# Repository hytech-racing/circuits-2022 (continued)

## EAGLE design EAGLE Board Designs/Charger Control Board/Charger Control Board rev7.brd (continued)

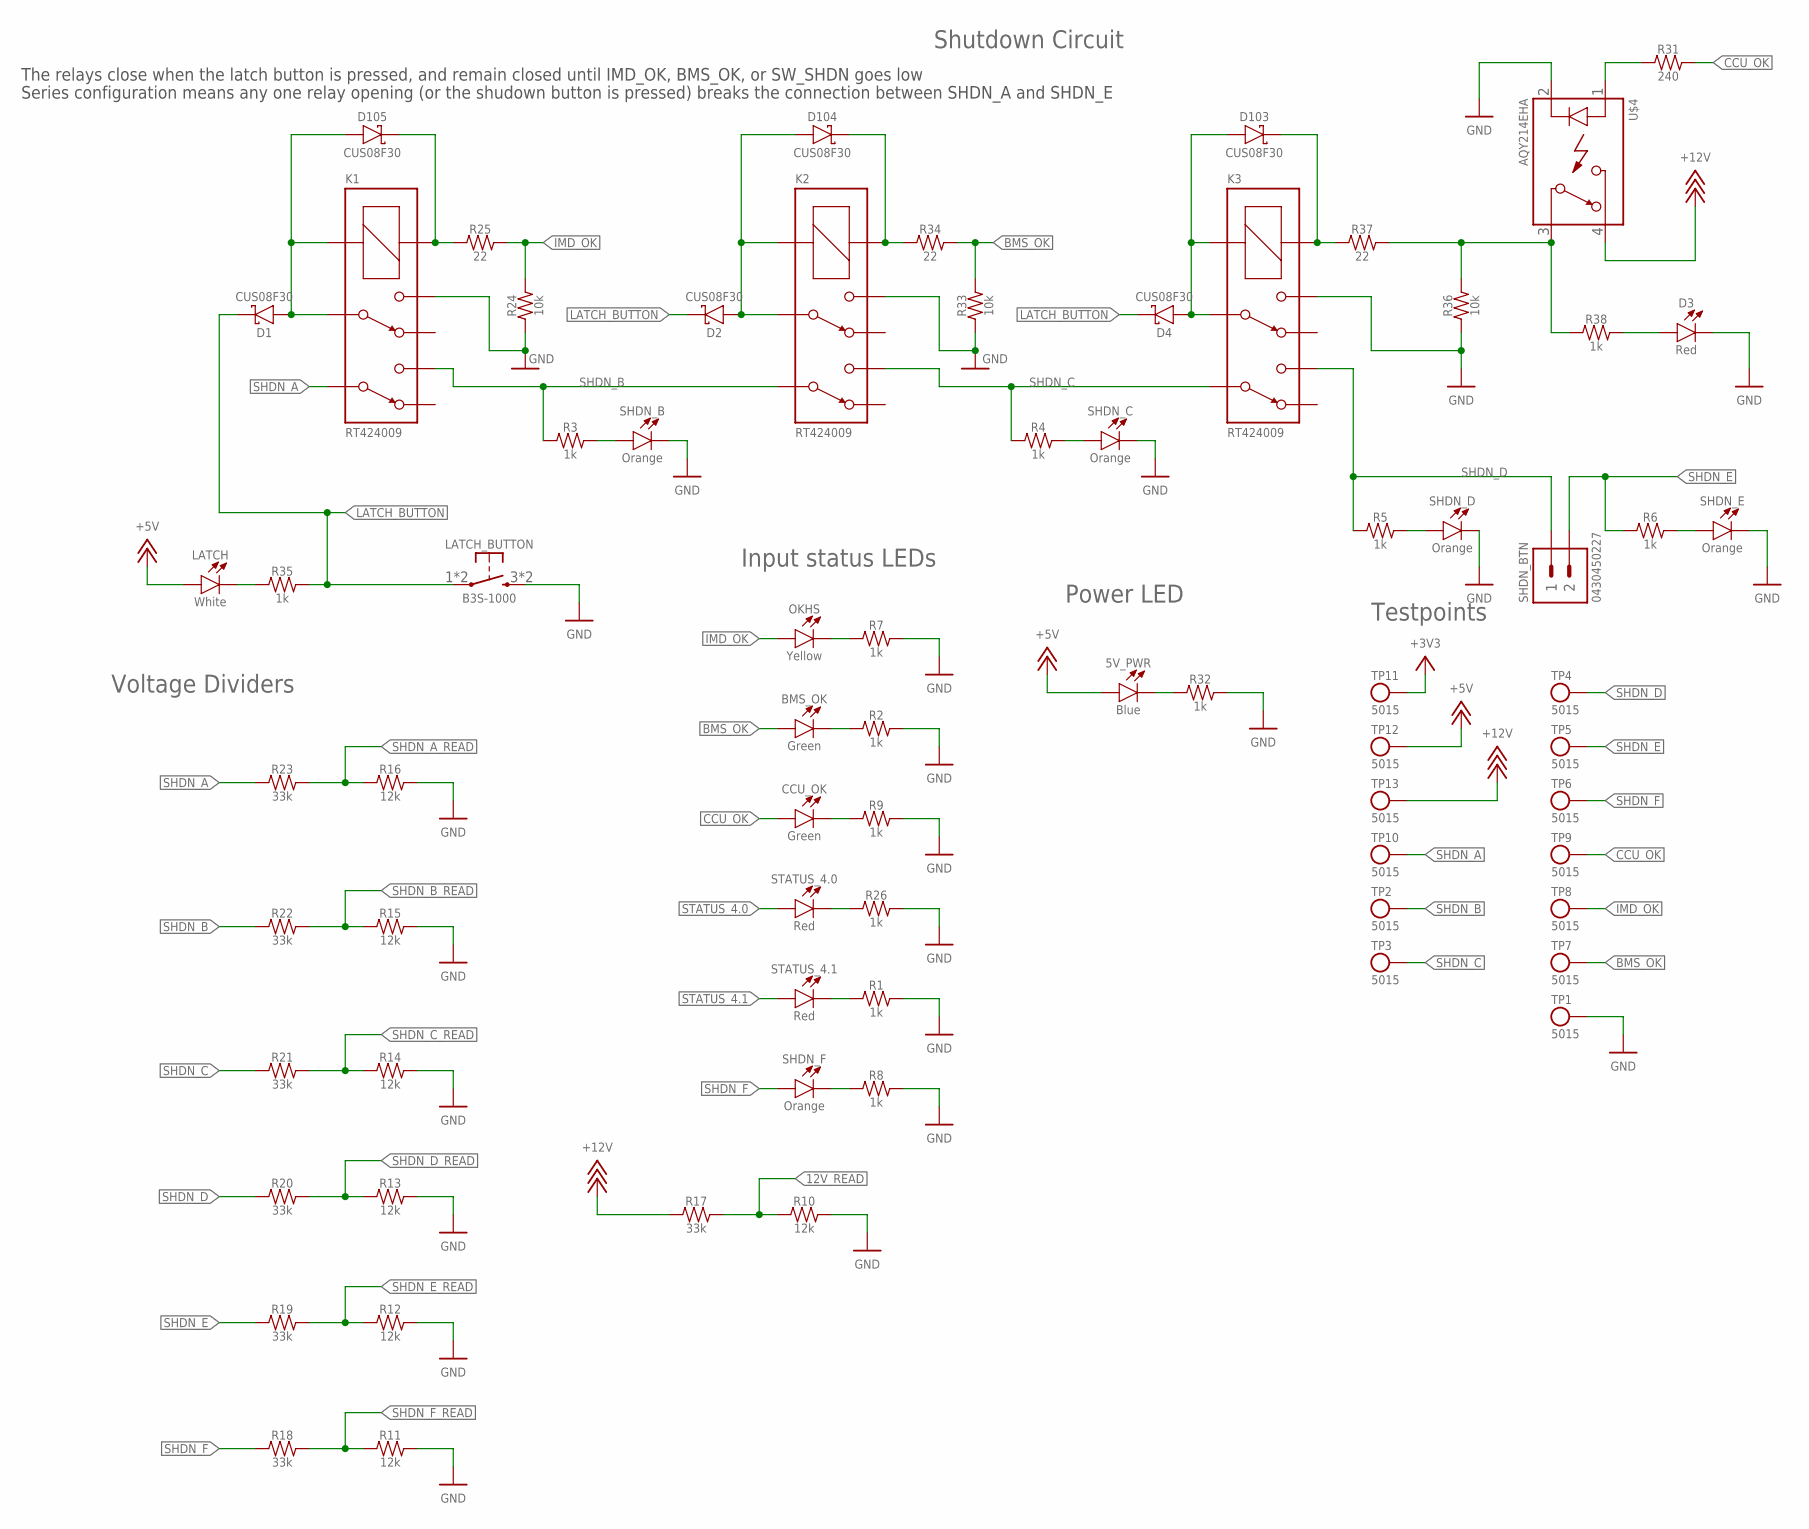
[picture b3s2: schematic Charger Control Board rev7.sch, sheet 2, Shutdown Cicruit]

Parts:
5V_PWR: LED_0603_BLUE; 0603-LED
BMS_OK: LED_0603_GREEN; 0603-LED
CCU_OK: LED_0603_GREEN; 0603-LED
D1, D2, D4, D103, D104, D105: SCHOTTKY_SOD323_30V; SOD-323
D3: LED_0603_RED; 0603-LED
K1, K2, K3: RELAY_DPDT; RT*2*
LATCH: LED_0603_WHITE; 0603-LED
LATCH_BUTTON: BUTTON; B3S-100X
OKHS: LED_0603_YELLOW; 0603-LED
R1, R2, R3, R4, R5, R6, R7, R8, R9, R26, R32, R35, R38: RESISTOR_0603_1K; 0603-RES
R10, R11, R12, R13, R14, R15, R16: RESISTOR_0603_12K; 0603-RES
R17, R18, R19, R20, R21, R22, R23: RESISTOR_0603_33K; 0603-RES
R24, R33, R36: RESISTOR_0603_10K; 0603-RES
R25, R34, R37: RESISTOR_0603_22; 0603-RES
R31: RESISTOR_0603_240; 0603-RES
SHDN_B: LED_0603_ORANGE; 0603-LED
SHDN_BTN: CONNECTOR-2_μF_T_V_; MOLEX_MICROFIT_PTH_VERTICAL_02_DUAL
SHDN_C: LED_0603_ORANGE; 0603-LED
SHDN_D: LED_0603_ORANGE; 0603-LED
SHDN_E: LED_0603_ORANGE; 0603-LED
SHDN_F: LED_0603_ORANGE; 0603-LED
STATUS_4.0, STATUS_4.1: LED_0603_RED; 0603-LED
TP1, TP2, TP3, TP4, TP5, TP6, TP7, TP8, TP9, TP10, TP11, TP12, TP13: TEST_POINT; 5015
U$4: RELAY_SOLIDSTATE_NO; DIP-4

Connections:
12V_READ: R10.1, R17.2; also elsewhere on the board
+3V3: TP11.1; also elsewhere on the board
+5V: 5V_PWR.2 (A), LATCH.2 (A), TP12.1; also elsewhere on the board
+12V: R17.1, TP13.1, U$4.4 (CONTACT2); also elsewhere on the board
BMS_OK: BMS_OK.2 (A), R33.2, R34.2, TP7.1; also elsewhere on the board
CCU_OK: CCU_OK.2 (A), R31.2, TP9.1; also elsewhere on the board
GND: D3.1 (C), K1.14 (4), K2.14 (4), K3.14 (4), LATCH_BUTTON.3 (S), LATCH_BUTTON.4 (S), R1.2, R2.2, R7.2, R8.2, R9.2, R10.2, R11.2, R12.2, R13.2, R14.2, R15.2, R16.2, R24.1, R26.2, R32.2, R33.1, R36.1, SHDN_B.1 (C), SHDN_C.1 (C), SHDN_D.1 (C), SHDN_E.1 (C), TP1.1, U$4.2 (CONTROL-); also elsewhere on the board
IMD_OK: OKHS.2 (A), R24.2, R25.2, TP8.1; also elsewhere on the board
LATCH_BUTTON: D1.C, D2.C, D4.C, LATCH_BUTTON.1, LATCH_BUTTON.2, R35.2
unnamed: R8.1, SHDN_F.1 (C)
unnamed: R31.1, U$4.1 (CONTROL+)
unnamed: D1.A, D105.A, K1.11 (3), K1.A2 (COIL-)
unnamed: D105.C, K1.A1 (COIL+), R25.1
unnamed: D104.C, K2.A1 (COIL+), R34.1
unnamed: D2.A, D104.A, K2.11 (3), K2.A2 (COIL-)
unnamed: D103.C, K3.A1 (COIL+), R37.1
unnamed: R36.2, R37.2, R38.1, U$4.3 (CONTACT1)
unnamed: LATCH.1 (C), R35.1
unnamed: R5.2, SHDN_D.2 (A)
unnamed: R6.2, SHDN_E.2 (A)
unnamed: D4.A, D103.A, K3.11 (3), K3.A2 (COIL-)
unnamed: D3.2 (A), R38.2
unnamed: R4.2, SHDN_C.2 (A)
unnamed: R3.2, SHDN_B.2 (A)
unnamed: OKHS.1 (C), R7.1
unnamed: BMS_OK.1 (C), R2.1
unnamed: CCU_OK.1 (C), R9.1
unnamed: R26.1, STATUS_4.0.1 (C)
unnamed: 5V_PWR.1 (C), R32.1
unnamed: R1.1, STATUS_4.1.1 (C)
SHDN_A: K1.21 (6), R23.1, TP10.1; also elsewhere on the board
SHDN_A_READ: R16.1, R23.2; also elsewhere on the board
SHDN_B: K1.24 (5), K2.21 (6), R3.1, R22.1, TP2.1
SHDN_B_READ: R15.1, R22.2; also elsewhere on the board
SHDN_C: K2.24 (5), K3.21 (6), R4.1, R21.1, TP3.1
SHDN_C_READ: R14.1, R21.2; also elsewhere on the board
SHDN_D: K3.24 (5), R5.1, R20.1, SHDN_BTN.1, TP4.1
SHDN_D_READ: R13.1, R20.2; also elsewhere on the board
SHDN_E: R6.1, R19.1, SHDN_BTN.2, TP5.1; also elsewhere on the board
SHDN_E_READ: R12.1, R19.2; also elsewhere on the board
SHDN_F: R18.1, SHDN_F.2 (A), TP6.1; also elsewhere on the board
SHDN_F_READ: R11.1, R18.2; also elsewhere on the board
STATUS_4.0: STATUS_4.0.2 (A); also elsewhere on the board
STATUS_4.1: STATUS_4.1.2 (A); also elsewhere on the board

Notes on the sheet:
Input status LEDs
Power LED
Voltage Dividers
Shutdown Circuit
Testpoints
The relays close when the latch button is pressed, and remain closed until IMD_OK, BMS_OK, or SW_SHDN goes low
Series configuration means any one relay opening (or the shudown button is pressed) breaks the connection between SHDN_A and SHDN_E

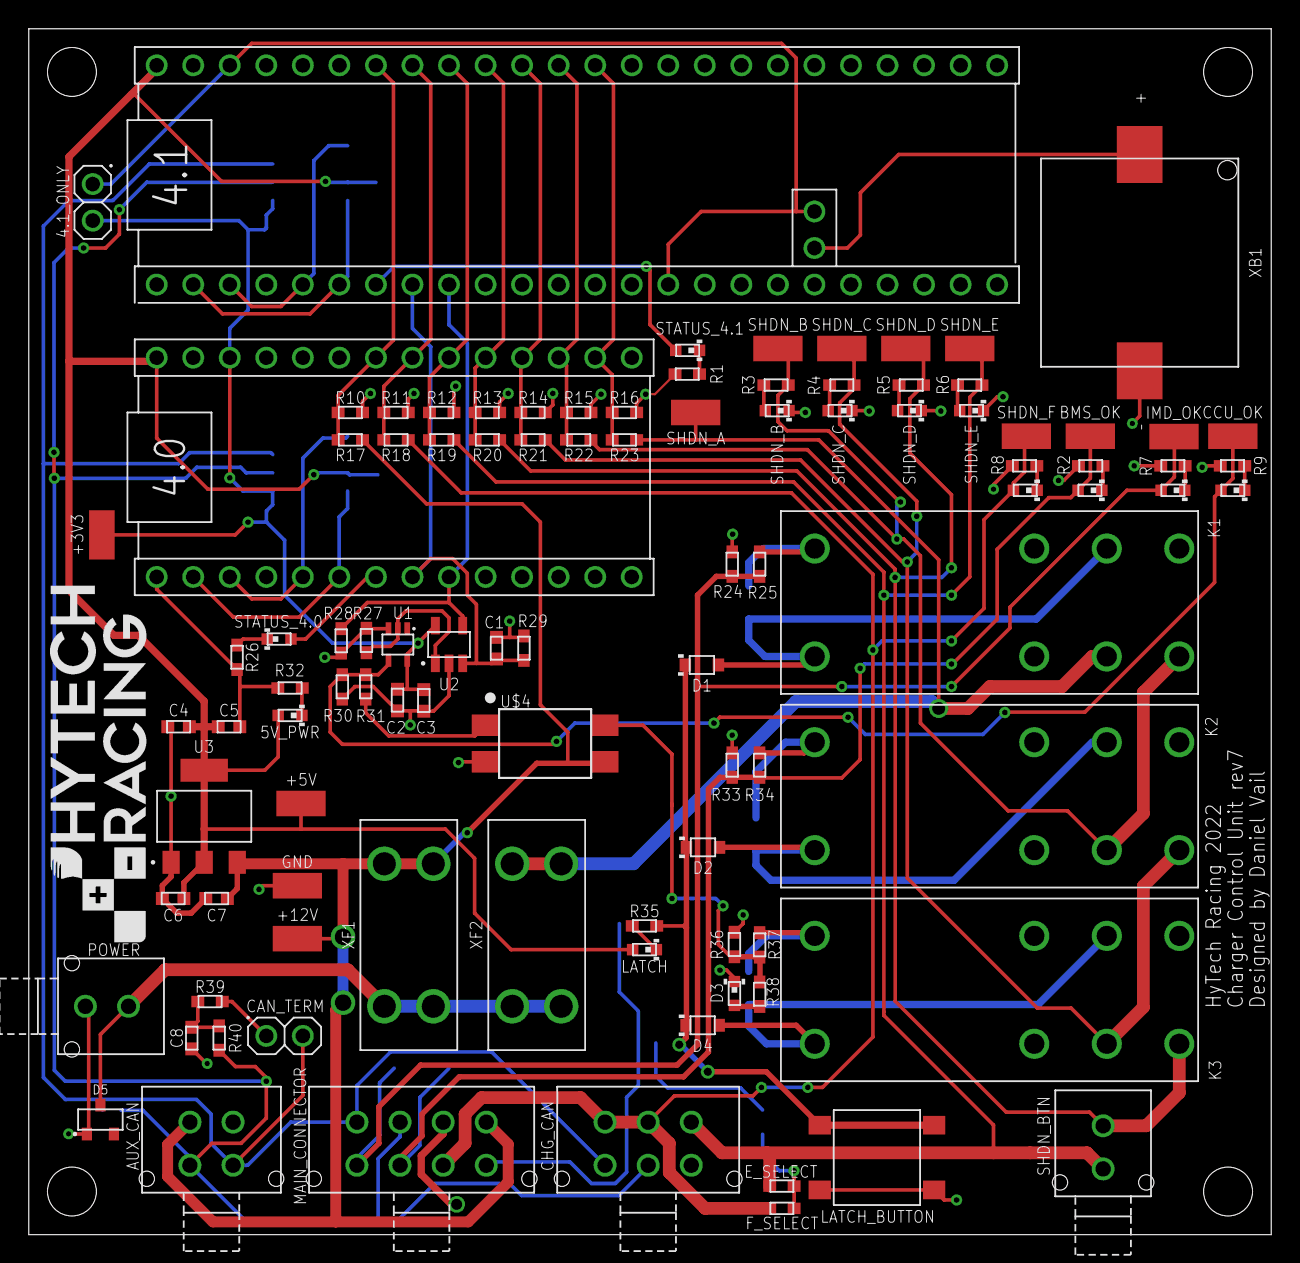
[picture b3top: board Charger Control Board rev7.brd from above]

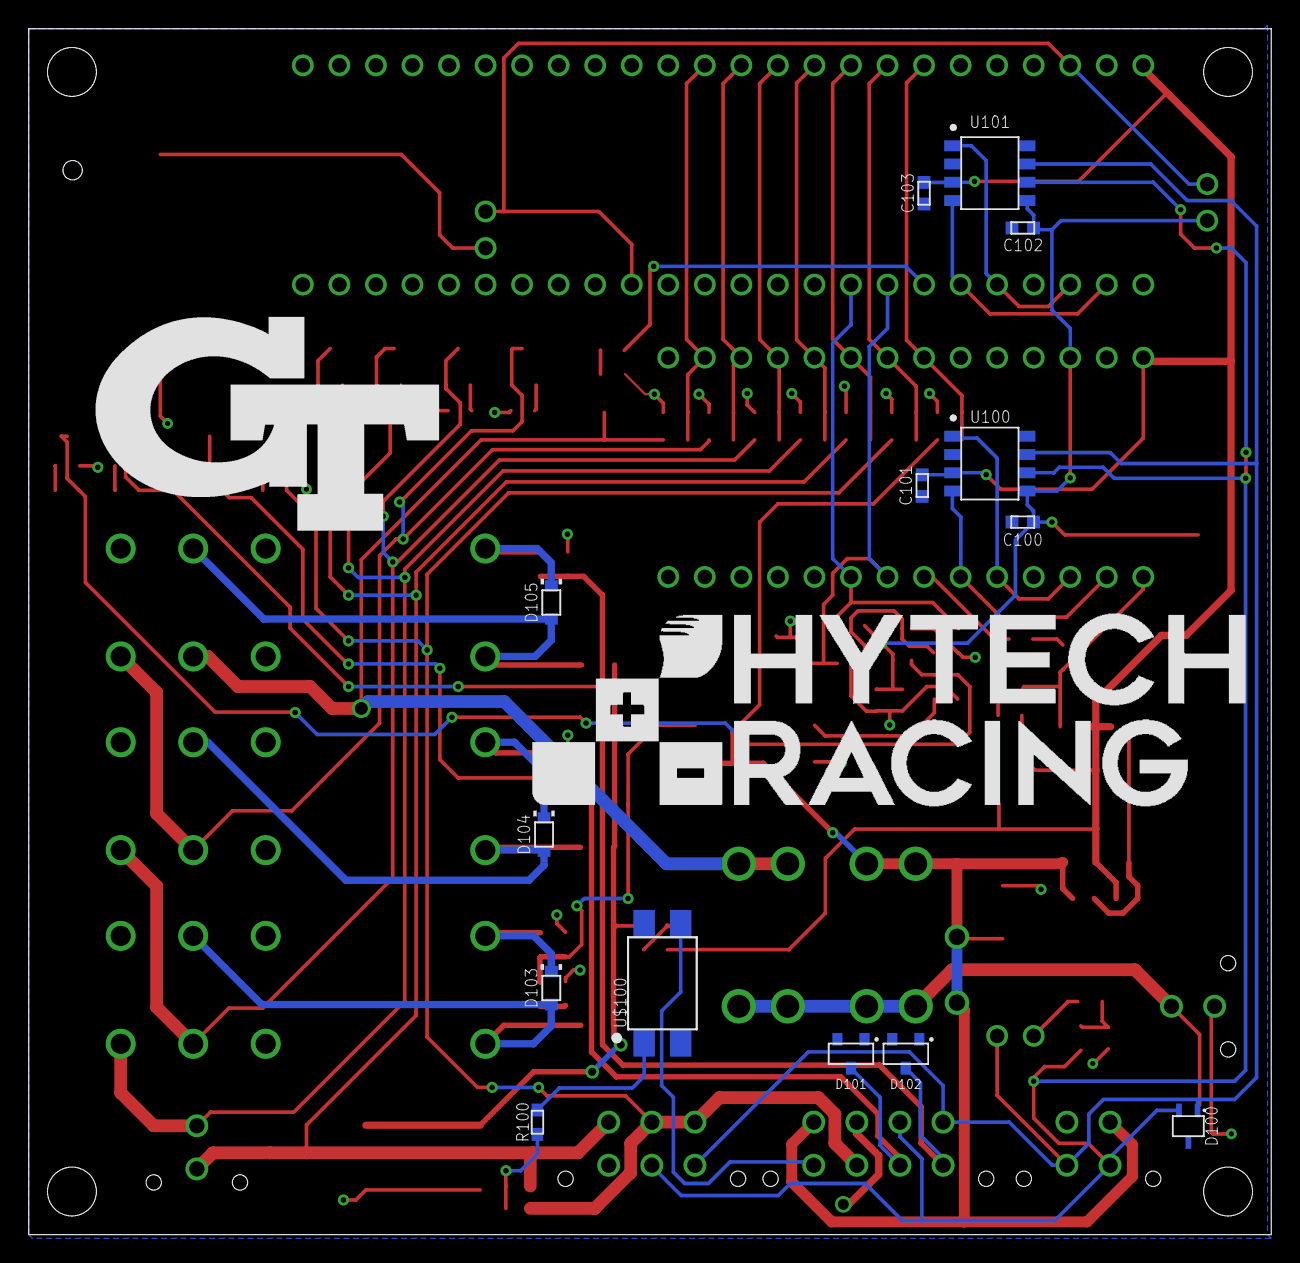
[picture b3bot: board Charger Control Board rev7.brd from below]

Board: 2 copper layers, 86.4 x 83.8 mm, 121 parts (16 on the bottom side), 61 nets.

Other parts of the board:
U$1, U$2, U$6, U$7: MOUNTING_M3
U$5: LOGO_HYTECH_MEDIUM
U$9: LOGO_HYTECH_LARGE
U$10: LOGO_GT_LARGE

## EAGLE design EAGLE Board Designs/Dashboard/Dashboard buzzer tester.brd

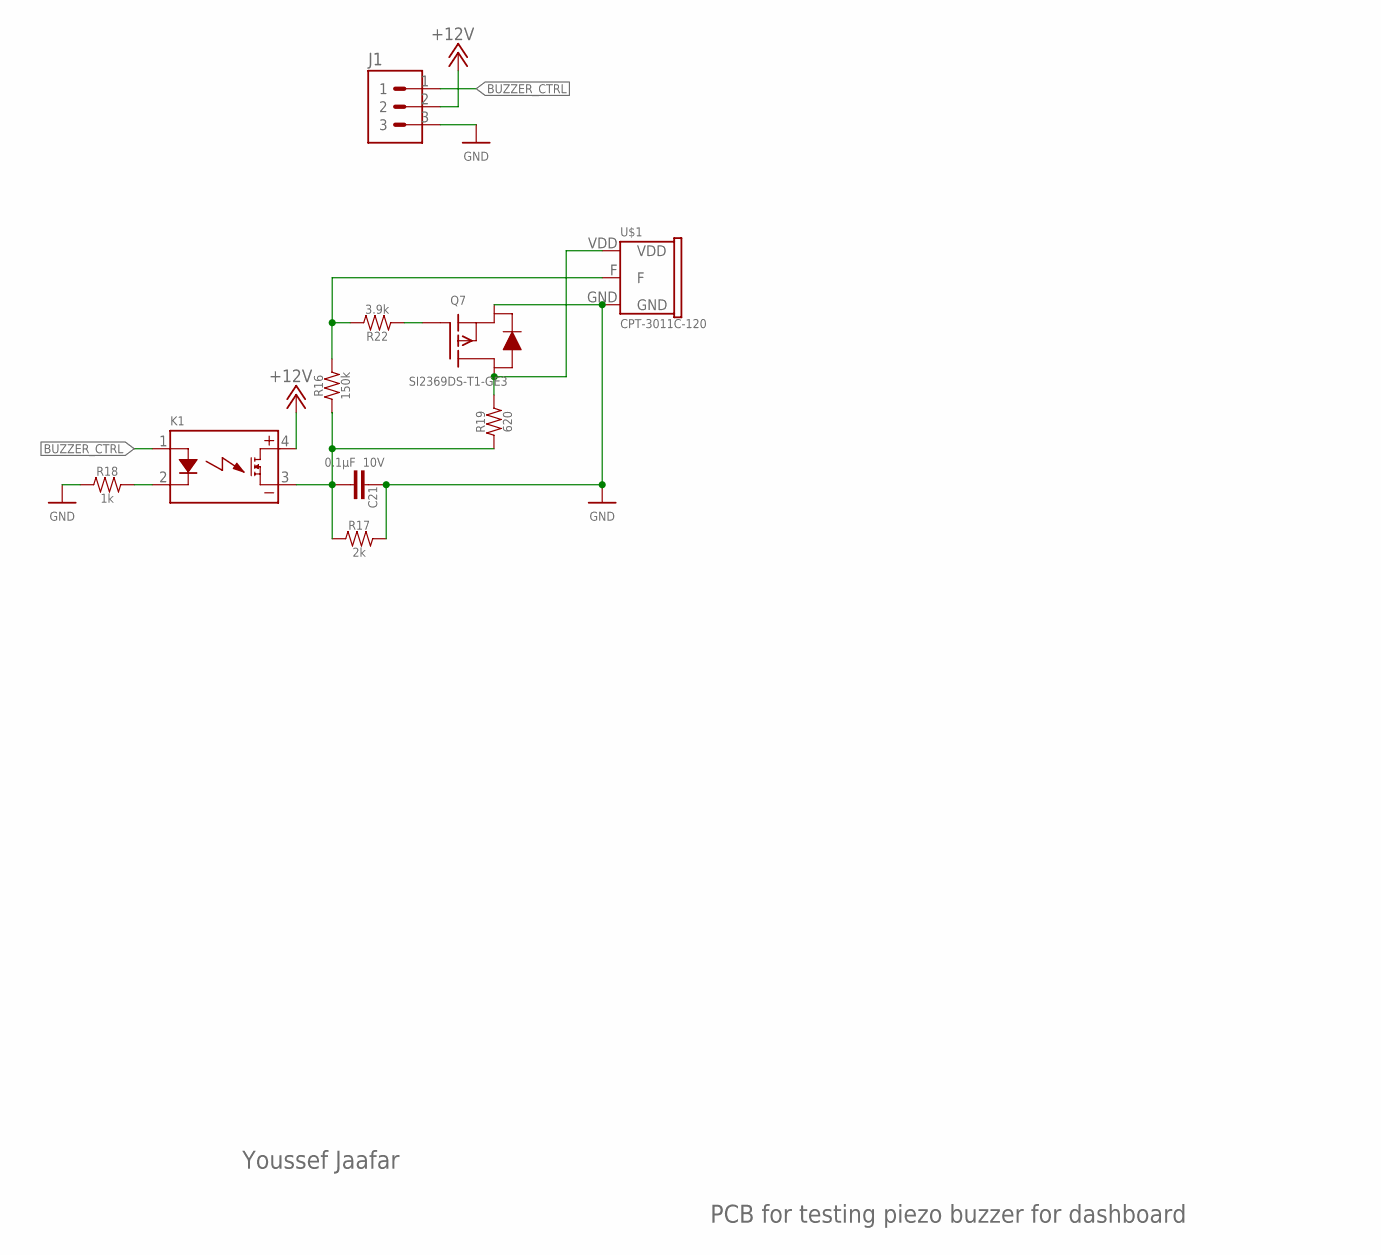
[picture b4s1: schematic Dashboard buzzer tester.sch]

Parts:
C21: CAPACITOR_0603_10V_0.1UF; 0603-CAP
J1: CONNECTOR-3; 1X03
K1: CPC1002N; SOP-04
Q7: TRANSISTOR_P_MOS_SOT23_SI2369DS-T1-GE3; SOT-23
R16: RESISTOR_0603_150K; 0603-RES
R17: RESISTOR_0603_2K; 0603-RES
R18: RESISTOR_0603_1K; 0603-RES
R19: RESISTOR_0603_620; 0603-RES
R22: RESISTOR_0603_3.9K; 0603-RES
U$1: BUZZER_3_PIN_CPT-3011C-120; CPT-3011C-120

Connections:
+12V: J1.2, K1.4 (DC+)
BUZZER_CTRL: J1.1, K1.1 (CONTROL+)
BUZZER_OUT: C21.1, K1.3 (DC-), R16.1, R17.1, R19.1
GND: C21.2, J1.3, Q7.2 (S), R17.2, R18.1, U$1.GND
unnamed: Q7.3 (D), R19.2, U$1.VDD
unnamed: Q7.1 (G), R22.1
unnamed: R16.2, R22.2, U$1.F
unnamed: K1.2 (CONTROL-), R18.2

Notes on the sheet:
Youssef Jaafar
PCB for testing piezo buzzer for dashboard

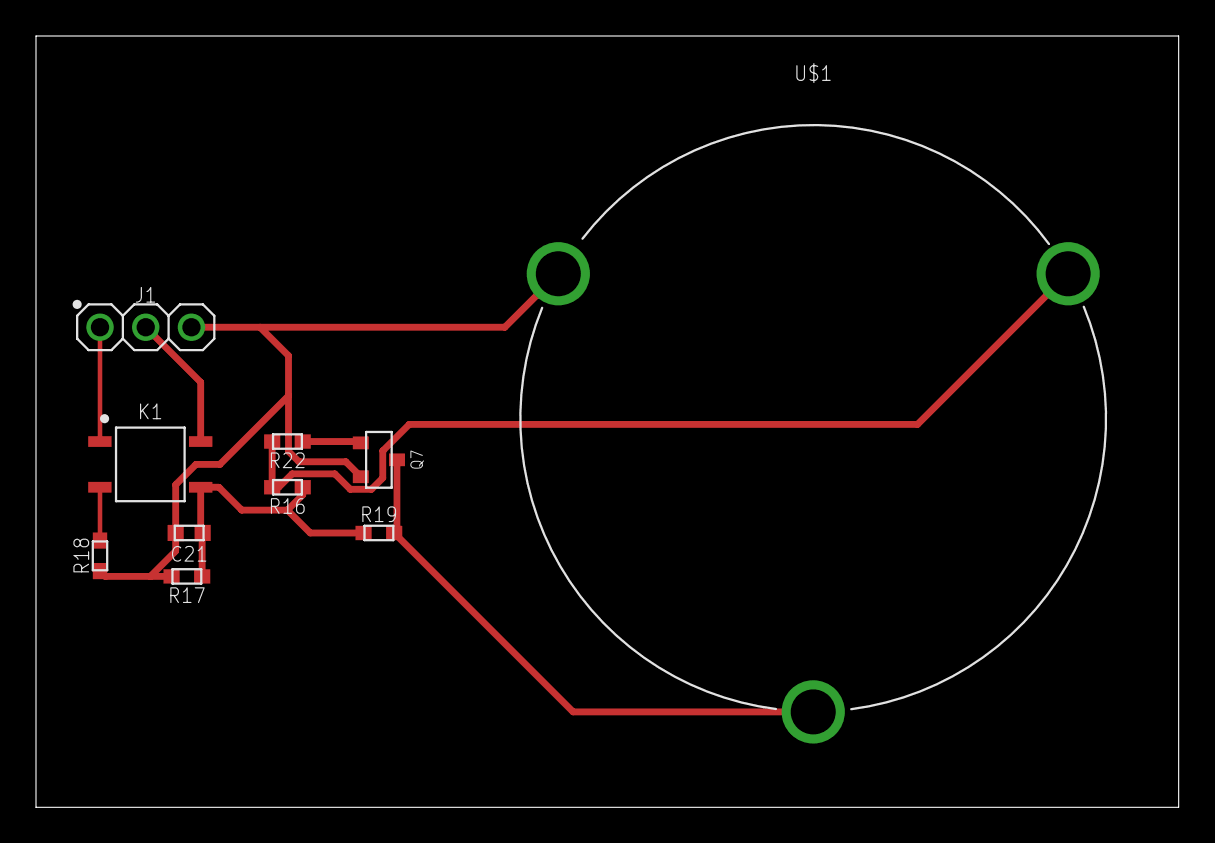
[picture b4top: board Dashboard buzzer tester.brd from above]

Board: 2 copper layers, 63.5 x 42.9 mm, 10 parts (0 on the bottom side), 8 nets.

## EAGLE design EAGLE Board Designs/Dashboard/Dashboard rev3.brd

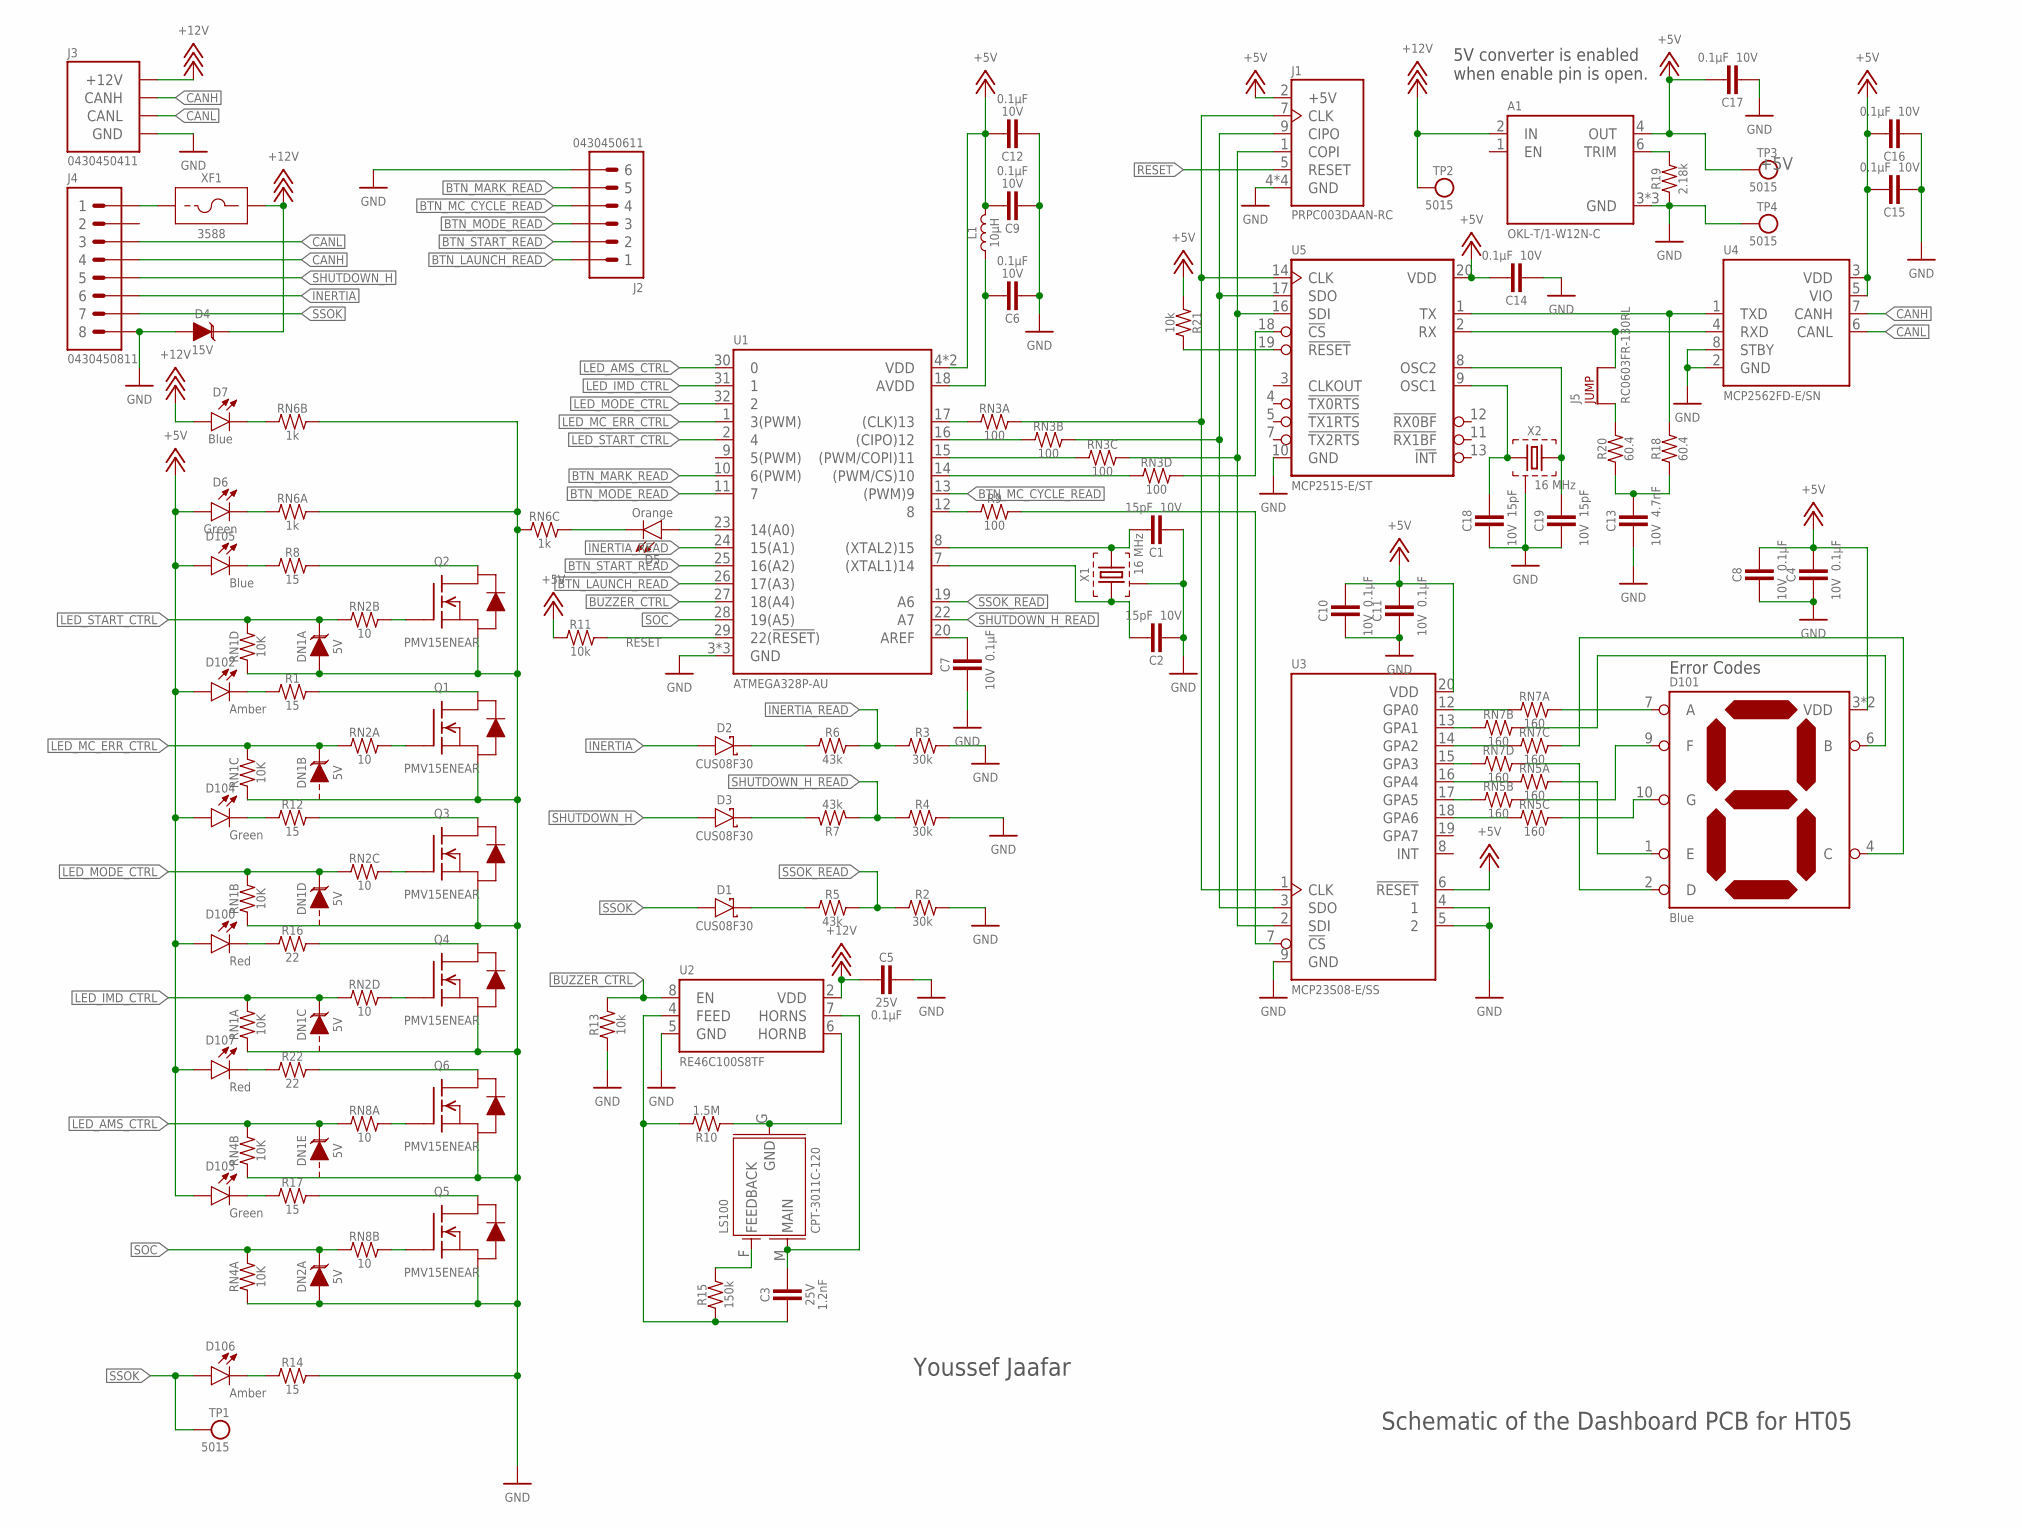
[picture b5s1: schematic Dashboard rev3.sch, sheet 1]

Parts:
A1: OKL-T/1-W12N-COKL; OKL-T/1-W12
C1, C2, C18, C19: CAPACITOR_0603_10V_15PF; 0603-CAP
C3: CAPACITOR_0603_25V_1.2NF; 0603-CAP
C4, C6, C7, C8, C9, C10, C11, C12, C14, C15, C16, C17: CAPACITOR_0603_10V_0.1UF; 0603-CAP
C5: CAPACITOR_0603_25V_0.1UF; 0603-CAP
C13: CAPACITOR_0603_10V_4.7NF; 0603-CAP
D1, D2, D3: SCHOTTKY_SOD323_30V; SOD-323
D4: TVS_15V; SOT-23
D5: LED_0603_ORANGE; 0603-LED
D6: LED_0603_GREEN; 0603-LED
D7: LED_0603_BLUE; 0603-LED
D100, D107: LED_2835_RED; 2835-LED
D101: LED_7_SEGMENT_BLUE_DSM7TA; DSM7T
D102, D106: LED_2835_AMBER; 2835-LED
D103, D104: LED_2835_GREEN; 2835-LED
D105: LED_2835_BLUE; 2835-LED
DN1, DN2: TVS_ARRAY_5V; SOT-363
J1: CONNECTOR-AVR-ISP_2X05_SMD; 2X05_SMD
J2: CONNECTOR-6_μF_S_RA_; MOLEX_MICROFIT_SMD_RIGHTANGLE_06_DUAL
J3: CONNECTOR-CAN_μF_S_RA_; MOLEX_MICROFIT_SMD_RIGHTANGLE_04_DUAL
J4: CONNECTOR-8_μF_S_RA_; MOLEX_MICROFIT_SMD_RIGHTANGLE_08_DUAL
J5: JUMPER_0603_; 0603-RES
L1: INDUCTOR_LQM18DH100M70_10UH; 0603-IND
LS100: BUZZER_3_PIN_CPT-3011C-120; CPT-3011C-120
Q1, Q2, Q3, Q4, Q5, Q6: TRANSISTOR_N_MOS__PMV15ENEA; SOT-23
R1, R8, R12, R14, R17: RESISTOR_0603_15; 0603-RES
R2, R3, R4: RESISTOR_0603_30K; 0603-RES
R5, R6, R7: RESISTOR_0603_43K; 0603-RES
R9: RESISTOR_0603_100; 0603-RES
R10: RESISTOR_0603_1.5M; 0603-RES
R11, R13, R21: RESISTOR_0603_10K; 0603-RES
R15: RESISTOR_0603_150K; 0603-RES
R16, R22: RESISTOR_0805_22; 0805-RES
R18, R20: RESISTOR_0603_60.4; 0603-RES
R19: RESISTOR_0603_2.18K; 0603-RES
RN1, RN4: RESISTOR_NETWORK_4_10K; 1206-RES-ARRAY
RN2, RN8: RESISTOR_NETWORK_4_10; 1206-RES-ARRAY
RN3: RESISTOR_NETWORK_4_100; 1206-RES-ARRAY
RN5, RN7: RESISTOR_NETWORK_4_160; 1206-RES-ARRAY
RN6: RESISTOR_NETWORK_4_1K; 1206-RES-ARRAY
TP1, TP2, TP3, TP4: TEST_POINT; 5015
U1: ATMEGA328P-AU; TQFP-32
U2: RE46C100; SOIC-08(NARROW,0.15")
U3: MCP23S08; SSOP-20
U4: MCP2562FD; SOIC-08(NARROW,0.15")
U5: MCP2515; TSSOP-20
X1, X2: CRYSTAL_16MHZ; ECX-42
XF1: FUSE_HOLDER_MINIBLADESMD; 3588

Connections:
+5V: A1.4 (OUT), C4.1, C8.1, C9.1, C10.1, C11.1, C12.1, C14.1, C15.1, C16.1, C17.1, D6.2 (A), D100.A, D101.3 (VDD), D101.8 (VDD), D102.A, D103.A, D104.A, D105.A, D107.A, J1.2 (+5V), L1.2, R11.1, R21.1, TP3.1, U1.4 (VDD), U1.6 (VDD), U3.6 (!RESET), U3.20 (VDD), U4.3 (VDD), U4.5 (VIO), U5.20 (VDD)
+12V: A1.2 (IN), C5.2, D4.3 (C), D7.2 (A), J3.1 (+12V), TP2.1, U2.2 (VDD), XF1.3 (2), XF1.4 (2)
A2: RN7.1, U3.12 (GPA0)
B2: RN7.2 (1), U3.13 (GPA1)
BTN_LAUNCH_READ: J2.1, U1.26 (17(A3))
BTN_MARK_READ: J2.5, U1.10 (6(PWM))
BTN_MC_CYCLE_READ: J2.4, U1.13 ((PWM)9)
BTN_MODE_READ: J2.3, U1.11 (7)
BTN_START_READ: J2.2, U1.25 (16(A2))
BUZZER_CTRL: R13.2, U1.27 (18(A4)), U2.8 (EN)
C2: RN7.3 (1), U3.14 (GPA2)
CANH: J3.4 (CANH), J4.4, U4.7 (CANH)
CANL: J3.3 (CANL), J4.3, U4.6 (CANL)
D2: RN7.4 (1), U3.15 (GPA3)
E2: RN5.1, U3.16 (GPA4)
F2: RN5.2 (1), U3.17 (GPA5)
G2: RN5.3 (1), U3.18 (GPA6)
GND: A1.3 (GND), A1.7 (GND), A1.11 (GND), C1.2, C2.2, C4.2, C5.1, C6.2, C7.2, C8.2, C9.2, C10.2, C11.2, C12.2, C13.2, C14.2, C15.2, C16.2, C17.2, C18.2, C19.2, D4.1 (A), DN1.2 (A), DN2.2 (A), J1.4 (GND), J1.6 (GND), J1.8 (GND), J1.10 (GND), J2.6, J3.2 (GND), J4.8, Q1.2 (S), Q2.2 (S), Q3.2 (S), Q4.2 (S), Q5.2 (S), Q6.2 (S), R2.2, R3.2, R4.2, R13.1, R14.2, R19.1, RN1.1, RN1.2 (1), RN1.3 (1), RN1.4 (1), RN4.1, RN4.2 (1), RN6.3 (1), RN6.7 (2), RN6.8 (2), TP4.1, U1.3 (GND), U1.5 (GND), U1.21 (GND), U2.5 (GND), U3.4 (1), U3.5 (2), U3.9 (GND), U4.2 (GND), U4.8 (STBY), U5.10 (GND), X1.2 (GND), X1.4 (GND), X2.2 (GND), X2.4 (GND)
INERTIA: D2.A, J4.6
INERTIA_READ: R3.1, R6.2, U1.24 (15(A1))
LED_AMS_CTRL: DN1.6 (C), RN4.7 (2), RN8.1, U1.30 (0)
LED_IMD_CTRL: DN1.4 (C), RN1.8 (2), RN2.4 (1), U1.31 (1)
LED_MC_ERR_CTRL: DN1.3 (C), RN1.6 (2), RN2.1, U1.1 (3(PWM))
LED_MODE_CTRL: DN1.5 (C), RN1.7 (2), RN2.3 (1), U1.32 (2)
LED_START_CTRL: DN1.1 (C), RN1.5 (2), RN2.2 (1), U1.2 (4)
unnamed: C18.1, U5.9 (OSC1), X2.1
unnamed: D102.C, R1.1
unnamed: C1.1, U1.8 ((XTAL2)15), X1.3
unnamed: C7.1, U1.20 (AREF)
unnamed: Q1.3 (D), R1.2
unnamed: Q3.3 (D), R12.2
unnamed: Q4.3 (D), R16.2
unnamed: Q6.3 (D), R22.2
unnamed: Q5.3 (D), R17.2
unnamed: Q2.1 (G), RN2.7 (2)
unnamed: C2.1, U1.7 ((XTAL1)14), X1.1
unnamed: J1.7 (CLK), RN3.8 (2), U3.1 (CLK), U5.14 (CLK)
unnamed: D101.7 (A), RN7.8 (2)
unnamed: D101.6 (B), RN7.7 (2)
unnamed: D101.4 (C), RN7.6 (2)
unnamed: D101.10 (G), RN5.6 (2)
unnamed: D101.9 (F), RN5.7 (2)
unnamed: D101.1 (E), RN5.8 (2)
unnamed: D101.2 (D), RN7.5 (2)
unnamed: RN3.4 (1), U1.14 ((PWM/CS)10)
unnamed: D6.1 (C), RN6.1
unnamed: Q1.1 (G), RN2.8 (2)
unnamed: J1.9 (CIPO), RN3.7 (2), U3.3 (SDO), U5.17 (SDO)
unnamed: D104.C, R12.1
unnamed: D100.C, R16.1
unnamed: D106.C, R14.1
unnamed: D107.C, R22.1
unnamed: C3.1, LS100.M (MAIN), U2.7 (HORNS)
unnamed: R9.1, U1.12 (8)
unnamed: A1.6 (TRIM), R19.2
unnamed: D105.C, R8.1
unnamed: D1.C, R5.1
unnamed: D3.C, R7.1
unnamed: Q2.3 (D), R8.2
unnamed: Q4.1 (G), RN2.5 (2)
unnamed: Q3.1 (G), RN2.6 (2)
unnamed: Q5.1 (G), RN8.7 (2)
unnamed: Q6.1 (G), RN8.8 (2)
unnamed: LS100.G (GND), R10.1, U2.6 (HORNB)
unnamed: D103.C, R17.1
unnamed: J5.2, U4.4 (RXD), U5.2 (RX)
unnamed: C19.1, U5.8 (OSC2), X2.3
unnamed: J4.1, XF1.1, XF1.2 (1)
unnamed: D5.2 (A), U1.23 (14(A0))
unnamed: RN3.1, U1.17 ((CLK)13)
unnamed: R21.2, U5.19 (!RESET)
unnamed: RN3.2 (1), U1.16 ((CIPO)12)
unnamed: RN3.3 (1), U1.15 ((PWM/COPI)11)
unnamed: C3.2, R10.2, R15.1, U2.4 (FEED)
unnamed: J5.1, R20.2
unnamed: C13.1, R18.1, R20.1
unnamed: R18.2, U4.1 (TXD), U5.1 (TX)
unnamed: LS100.F (FEEDBACK), R15.2
unnamed: J1.1 (COPI), RN3.6 (2), U3.2 (SDI), U5.16 (SDI)
unnamed: RN3.5 (2), U5.18 (!CS)
unnamed: R9.2, U3.7 (!CS)
unnamed: C6.1, L1.1, U1.18 (AVDD)
unnamed: D2.C, R6.1
RESET: J1.5 (RESET), R11.2, U1.29 (22(!RESET!))
SHUTDOWN_H: D3.A, J4.5
SHUTDOWN_H_READ: R4.1, R7.2, U1.22 (A7)
SOC: DN2.1 (C), RN4.8 (2), RN8.2 (1), U1.28 (19(A5))
SSOK: D1.A, D106.A, J4.7, TP1.1
SSOK_READ: R2.1, R5.2, U1.19 (A6)
STATUS_12V: D7.1 (C), RN6.2 (1)
STATUS_TEENSY: D5.1 (C), RN6.6 (2)

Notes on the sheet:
Youssef Jaafar
Schematic of the Dashboard PCB for HT05
Error Codes
5V converter is enabled when enable pin is open.

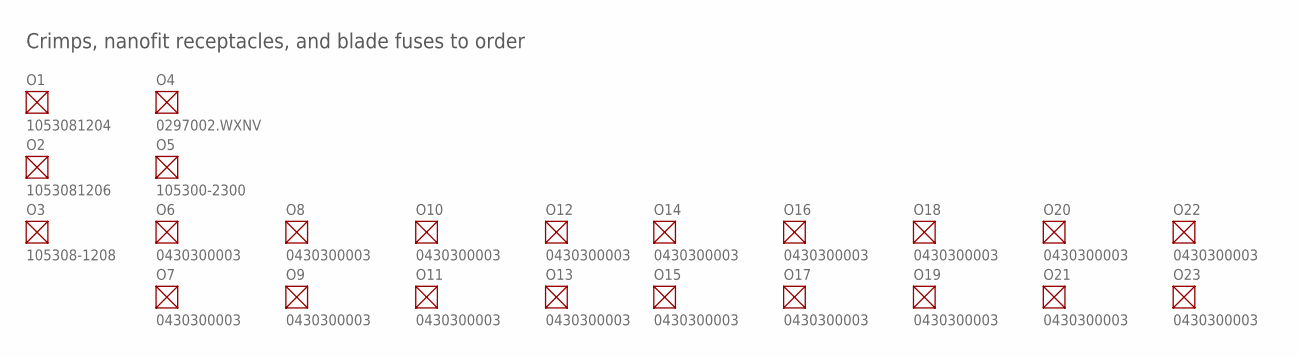
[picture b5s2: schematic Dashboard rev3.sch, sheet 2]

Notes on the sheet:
Crimps, nanofit receptacles, and blade fuses to order

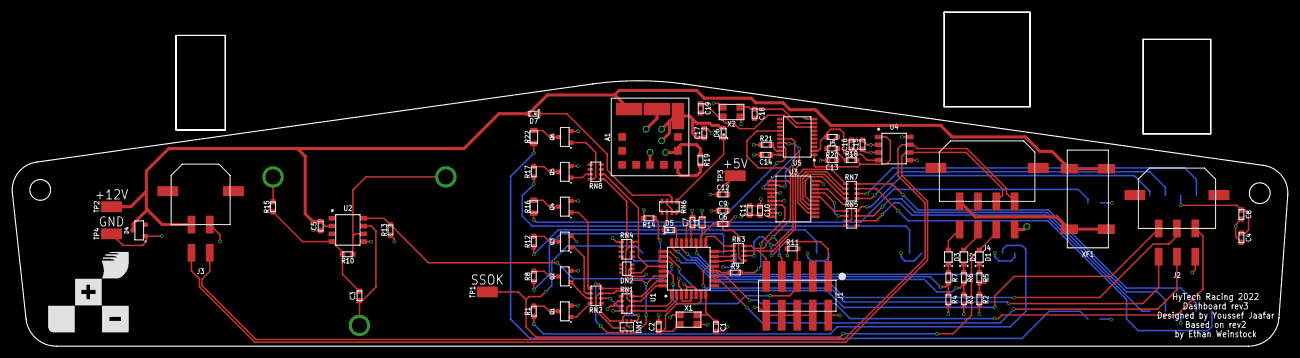
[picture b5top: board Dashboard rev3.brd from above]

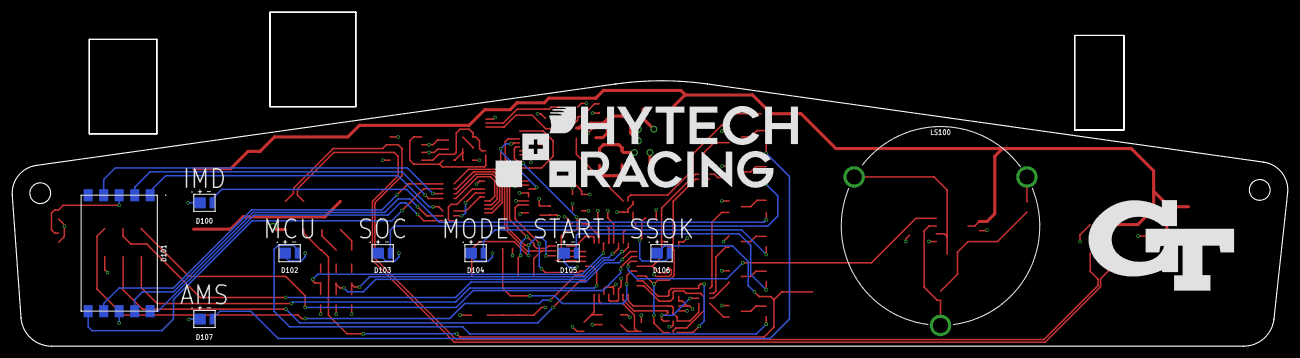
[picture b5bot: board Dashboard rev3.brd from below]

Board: 4 copper layers, 209.1 x 43.5 mm, 97 parts (11 on the bottom side), 91 nets.

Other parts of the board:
U$1, U$2: MOUNTING_M3
U$3: LOGO_HYTECH_SQUARE_EXTRA_LARGE
U$100: LOGO_HYTECH_LARGE
U$101: LOGO_GT_LARGE

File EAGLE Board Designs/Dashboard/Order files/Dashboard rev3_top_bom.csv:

Comment,Designator,Footprint,LCSC Part #
ATMEGA328P-AU,U1,TQFP-32,
CAPACITOR_0603_10V_0.1UF,C4 C6 C7 C8 C9 C10 C11 C12 C14 C15 C16 C17,0603-CAP,
CAPACITOR_0603_10V_4.7NF,C13,0603-CAP,
CAPACITOR_0603_10V_15PF,C1 C2 C18 C19,0603-CAP,
CAPACITOR_0603_25V_0.1UF,C5,0603-CAP,
CAPACITOR_0603_25V_1.2NF,C3,0603-CAP,
CONNECTOR-6_μF_S_RA_,J2,MOLEX_MICROFIT_SMD_RIGHTANGLE_06_DUAL,
CONNECTOR-8_μF_S_RA_,J4,MOLEX_MICROFIT_SMD_RIGHTANGLE_08_DUAL,
CONNECTOR-AVR-ISP_2X05_SMD,J1,2X05_SMD,
CONNECTOR-CAN_μF_S_RA_,J3,MOLEX_MICROFIT_SMD_RIGHTANGLE_04_DUAL,
CRYSTAL_16MHZ,X1 X2,ECX-42,
FUSE_HOLDER_MINIBLADESMD,XF1,3588,
INDUCTOR_LQM18DH100M70_10UH,L1,0603-IND,
JUMPER_0603_,J5,0603-RES,
LED_0603_BLUE,D7,0603-LED,
LED_0603_GREEN,D6,0603-LED,
LED_0603_ORANGE,D5,0603-LED,
MCP23S08,U3,SSOP-20,
MCP2515,U5,TSSOP-20,
MCP2562FD,U4,SOIC-08(NARROW 0.15"),
OKL-T/1-W12N-COKL,A1,OKL-T/1-W12,
RE46C100,U2,SOIC-08(NARROW 0.15"),
RESISTOR_0603_1.5M,R10,0603-RES,
RESISTOR_0603_2.18K,R19,0603-RES,
RESISTOR_0603_10K,R11 R13 R21,0603-RES,
RESISTOR_0603_22,R8,0603-RES,
RESISTOR_0603_30K,R2 R3 R4,0603-RES,
RESISTOR_0603_43K,R5 R6 R7,0603-RES,
RESISTOR_0603_60.4,R1 R14 R16 R18 R20 R22,0603-RES,
RESISTOR_0603_100,R9,0603-RES,
RESISTOR_0603_150K,R15,0603-RES,
RESISTOR_0603_180,R12 R17,0603-RES,
RESISTOR_NETWORK_4_1K,RN6,1206-RES-ARRAY,
RESISTOR_NETWORK_4_10,RN2 RN8,1206-RES-ARRAY,
RESISTOR_NETWORK_4_10K,RN1 RN4,1206-RES-ARRAY,
RESISTOR_NETWORK_4_100,RN3,1206-RES-ARRAY,
RESISTOR_NETWORK_4_160,RN5 RN7,1206-RES-ARRAY,
SCHOTTKY_SOD323_30V,D1 D2 D3,SOD-323,
TRANSISTOR_N_MOS__PMV15ENEA,Q1 Q2 Q3 Q4 Q5 Q6,SOT-23,
TVS_15V,D4,SOT-23,
TVS_ARRAY_5V,DN1 DN2,SOT-363,
